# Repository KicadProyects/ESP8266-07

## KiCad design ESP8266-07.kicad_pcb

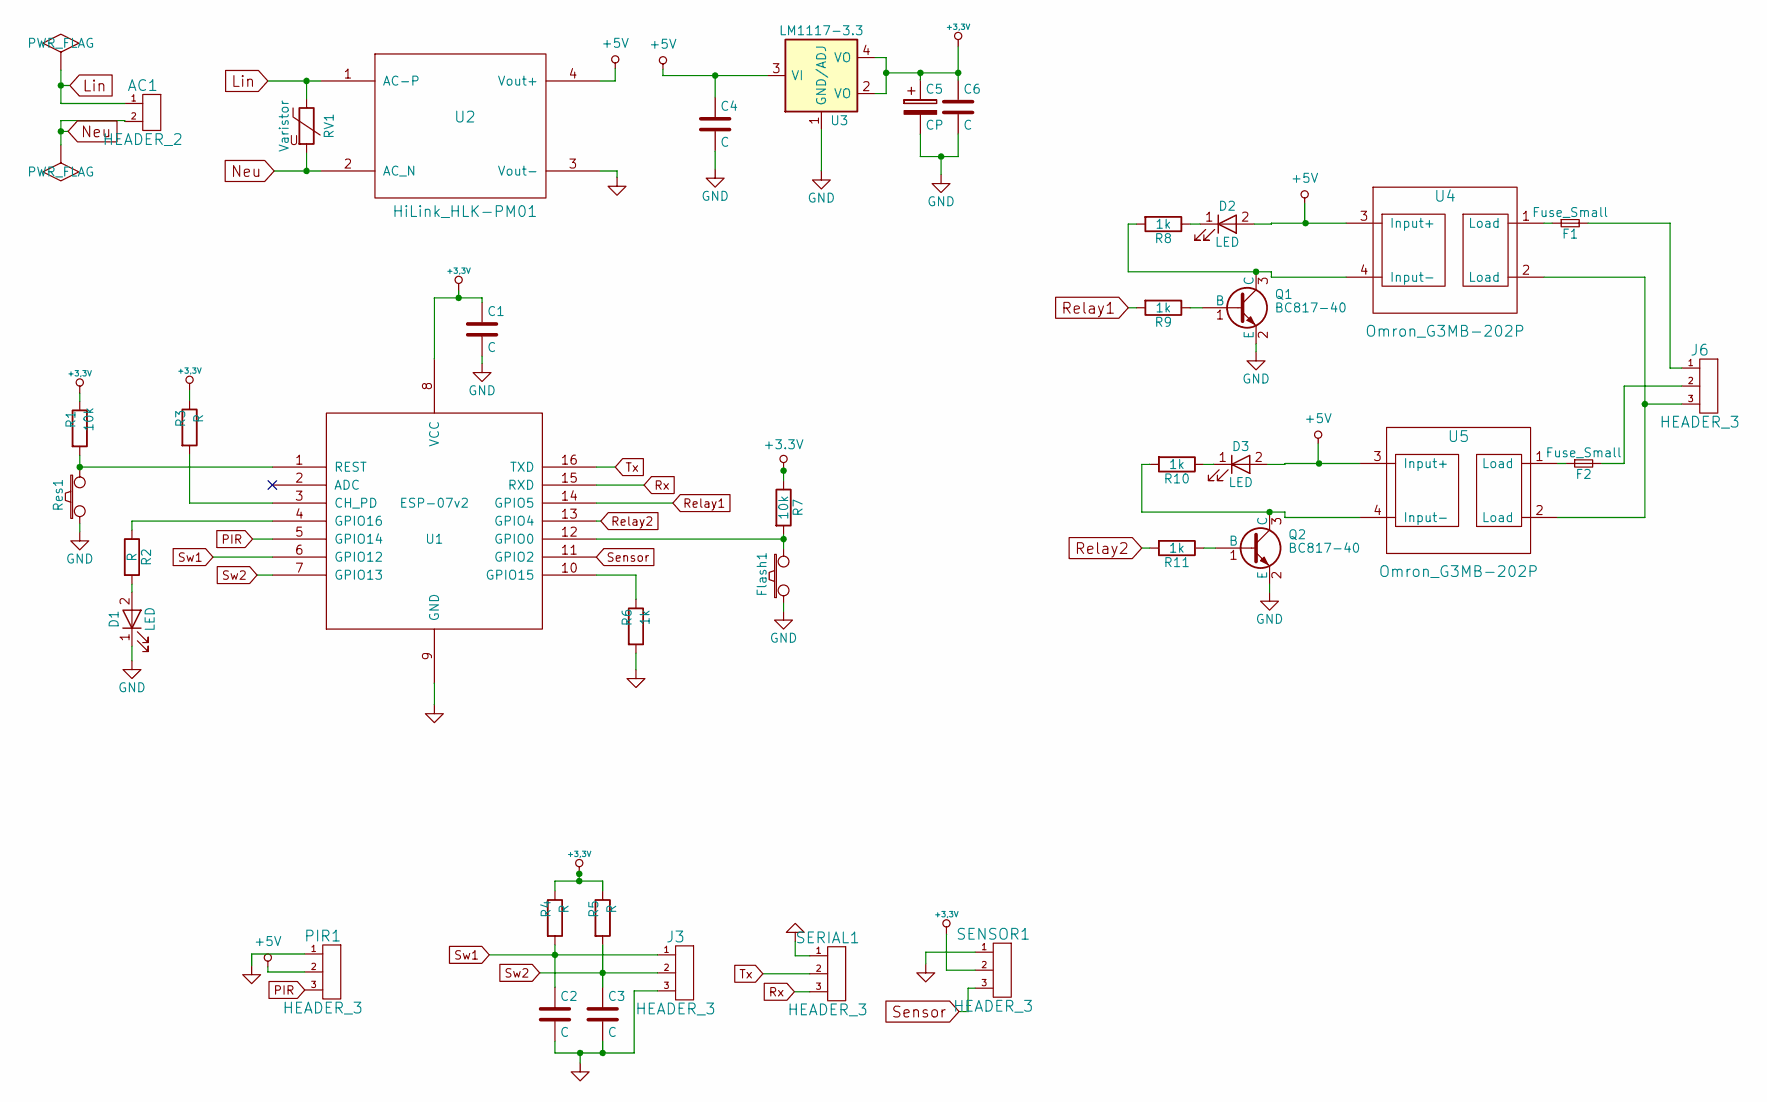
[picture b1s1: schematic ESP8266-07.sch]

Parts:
AC1: HEADER_2; mkds_1,5-2
C1, C2, C3, C4, C6: C; c_1206
C5: CP; CP_Tantalum_Case-U_EIA-6032-15_Wave
D1, D2, D3: LED; LED_1206
F1, F2: Fuse_Small; Fuse_SMD1206_Reflow
Flash1: SW_PUSH; smd_push
J3, J6: HEADER_3; mkds_1,5-3
PIR1: HEADER_3; pin_strip_2mm_3
Q1, Q2: BC817-40; sot23
R1, R7: 10k; r_1206
R2, R3, R4, R5: R; r_1206
R6, R8, R9, R10, R11: 1k; r_1206
RV1: Varistor; RV_Disc_D7_W3.4_P5
Res1: SW_PUSH; smd_push
SENSOR1: HEADER_3; pin_strip_2mm_3
SERIAL1: HEADER_3; pin_strip_2mm_3
U1: ESP-07v2
U2: HiLink_HLK-PM01; HLK-PM01
U3: LM1117-3.3; sot223
U4, U5: Omron_G3MB-202P

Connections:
+5V: C4.1, D2.2 (A), D3.2 (A), PIR1.2, U2.4 (Vout+), U3.3 (VI), U4.3 (Input+), U5.3 (Input+)
GND: C1.2, C2.2, C3.2, C4.2, C5.2, C6.2, D1.1 (K), Flash1.1, J3.3, PIR1.1, Q1.2 (E), Q2.2 (E), R6.2, Res1.1, SENSOR1.1, SERIAL1.1, U1.9 (GND), U2.3 (Vout-), U3.1 (GND/ADJ)
Lin: AC1.1, RV1.1, U2.1 (AC-P)
unnamed: D1.2 (A), R2.2
unnamed: D2.1 (K), R8.1
unnamed: D3.1 (K), R10.1
unnamed: F1.1, U4.1 (Load)
unnamed: F1.2, J6.1
unnamed: F2.1, U5.1 (Load)
unnamed: F2.2, J6.2
unnamed: Flash1.2, R7.2, U1.12 (GPIO0)
unnamed: J6.3, U4.2 (Load), U5.2 (Load)
unnamed: Q1.1 (B), R9.1
unnamed: Q1.3 (C), R8.2, U4.4 (Input-)
unnamed: Q2.1 (B), R11.1
unnamed: Q2.3 (C), R10.2, U5.4 (Input-)
unnamed: R1.2, Res1.2, U1.1 (REST)
unnamed: R2.1, U1.4 (GPIO16)
unnamed: R3.2, U1.3 (CH_PD)
unnamed: R6.1, U1.10 (GPIO15)
Neu: AC1.2, RV1.2, U2.2 (AC_N)
PIR: PIR1.3, U1.5 (GPIO14)
Relay1: R9.2, U1.14 (GPIO5)
Relay2: R11.2, U1.13 (GPIO4)
Rx: SERIAL1.3, U1.15 (RXD)
Sensor: SENSOR1.3, U1.11 (GPIO2)
Sw1: C2.1, J3.1, R4.2, U1.6 (GPIO12)
Sw2: C3.1, J3.2, R5.2, U1.7 (GPIO13)
Tx: SERIAL1.2, U1.16 (TXD)

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
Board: 2 copper layers, 36 parts (25 on the bottom side), 27 nets, no tracks yet.

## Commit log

2017-07-01 :space_invader: Added .gitattributes & .gitignore files
2017-07-02 first commit
    solo esquematico
2017-07-07 add model esp07
